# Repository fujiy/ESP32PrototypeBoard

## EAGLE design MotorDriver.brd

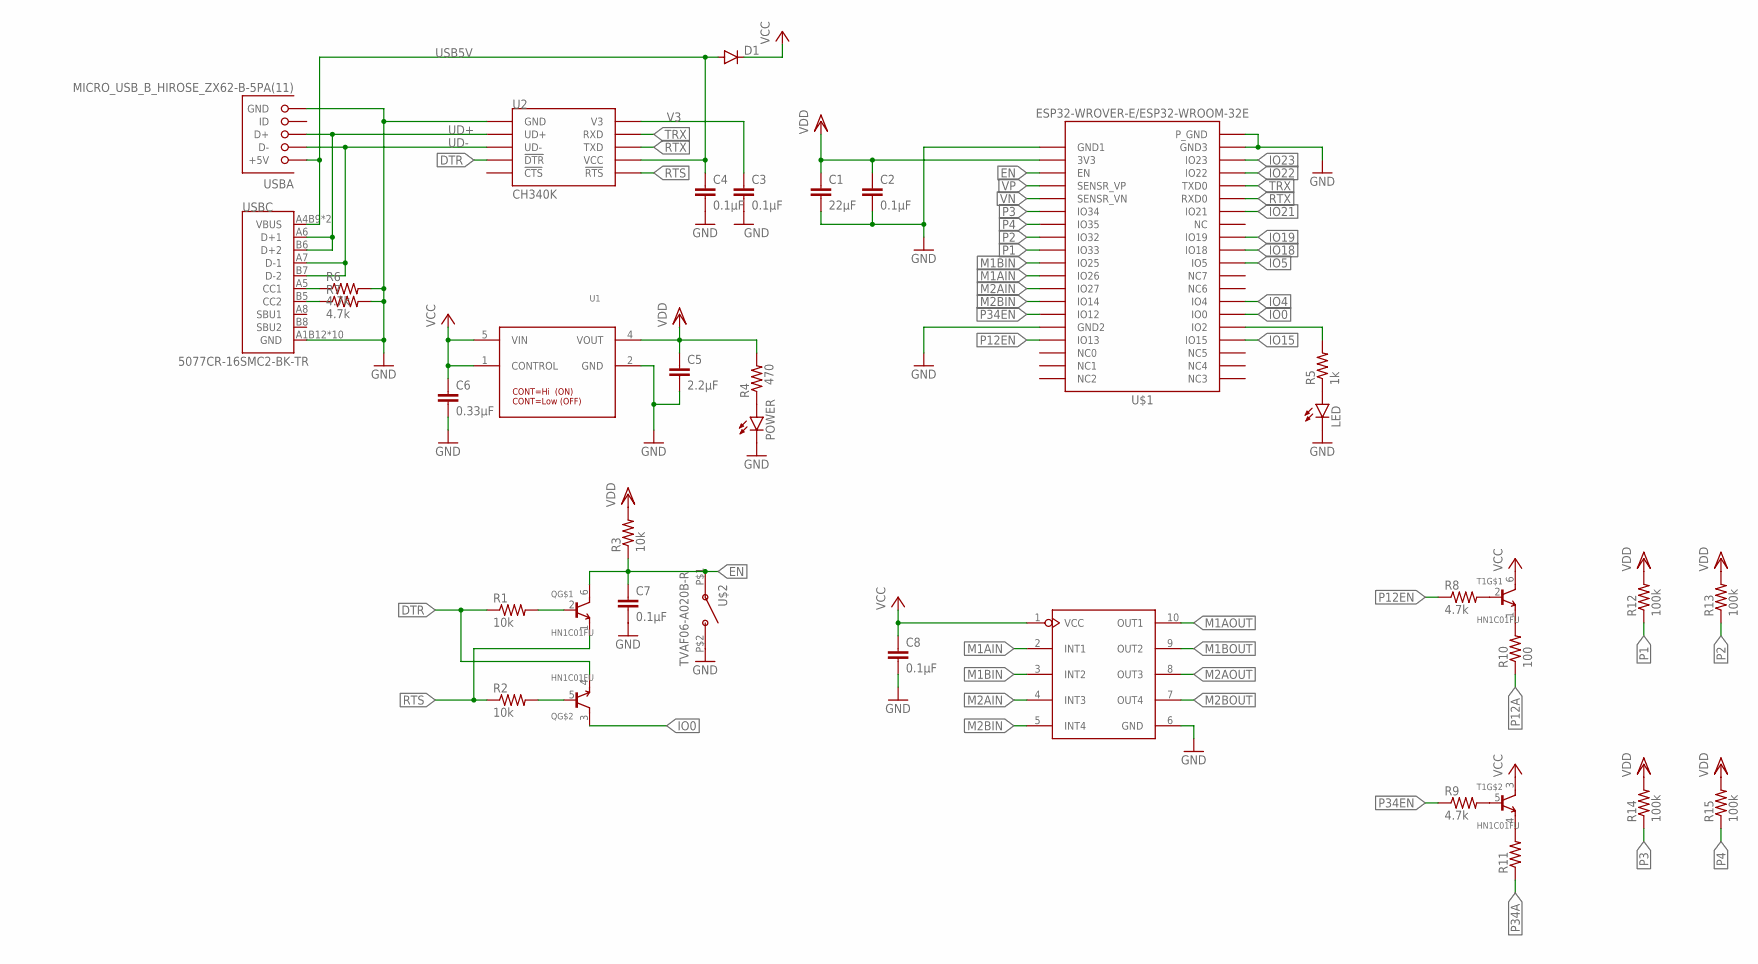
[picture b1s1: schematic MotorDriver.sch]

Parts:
C1: 22µF; C0603K
C2, C3, C4, C7: 0.1µF; C0603K
C5: 2.2µF; C0603K
C6: 0.33µF; C0603K
C8: 0.1µF; C0603
D1: DIODE-SOD123; SOD123
LED: LEDCHIPLED_0603; CHIPLED_0603
POWER: LEDCHIPLED_0603; CHIPLED_0603
Q: HN1C01FU; SOT-363
R1, R2, R3: 10k; R0603
R4: 470; R0603
R5: 1k; R0603
R6, R7, R8, R9: 4.7k; R0603
R10: 100; R0603
R11: R-US_R0603; R0603
R12, R13, R14, R15: 100k; R0603
T1: HN1C01FU; SOT-363
U1: I-10673_NJM2884U1-33; NJM2884U1-33
U2: CH340K; ESSOP-10
U3: DRIVER-LV8548MC-AH(SOIC10); SOIC10-1.0-5X4MM
U$1: ESP32-WROVER-E/ESP32-WROOM-32E
U$2: TVAF06-A020B-R
USBA: MICRO_USB_B_HIROSE_ZX62-B-5PA(11); USB_MICRO_B-HIROSE-ZX62-B-5PA(11)
USBC: 5077CR-16SMC2-BK-TR

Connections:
DTR: Q.4 (E), R1.1, U2.P4 (!DTR!)
EN: C7.1, Q.6 (C), R3.1, U$1.EN, U$2.P$1 (A)
GND: C1.2, C2.2, C3.2, C4.2, C5.2, C6.2, C7.2, C8.2, LED.C, POWER.C, R6.2, R7.2, U1.2 (GND), U2.P0 (GND), U2.P3 (GND), U3.6 (GND), U$1.GND1, U$1.GND2, U$1.GND2' (GND2), U$1.GND3, U$1.P_GND, U$2.P$2 (B), USBA.5 (GND), USBC.A1B12 (GND), USBC.B1A12 (GND), USBC.P$1 (GND), USBC.P$2 (GND), USBC.P$3 (GND), USBC.P$4 (GND), USBC.P$5 (GND), USBC.P$6 (GND), USBC.P$7 (GND), USBC.P$8 (GND)
IO0: Q.3 (C), U$1.IO0
IO2: R5.2, U$1.IO2, U$1.IO2' (IO2)
IO4: U$1.IO4
IO5: U$1.IO5
IO15: U$1.IO15, U$1.IO15' (IO15)
IO18: U$1.IO18
IO19: U$1.IO19
IO21: U$1.IO21
IO22: U$1.IO22
IO23: U$1.IO23
M1AIN: U3.2 (INT1), U$1.IO26
M1AOUT: U3.10 (OUT1)
M1BIN: U3.3 (INT2), U$1.IO25
M1BOUT: U3.9 (OUT2)
M2AIN: U3.4 (INT3), U$1.IO27
M2AOUT: U3.8 (OUT3)
M2BIN: U3.5 (INT4), U$1.IO14
M2BOUT: U3.7 (OUT4)
unnamed: LED.A, R5.1
unnamed: Q.2 (B), R1.2
unnamed: Q.5 (B), R2.2
unnamed: R8.2, T1.2 (B)
unnamed: R9.2, T1.5 (B)
unnamed: R10.2, T1.1 (E)
unnamed: R11.2, T1.4 (E)
unnamed: R6.1, USBC.A5 (CC1)
unnamed: POWER.A, R4.1
unnamed: R7.1, USBC.B5 (CC2)
P1: R12.1, U$1.IO33
P2: R13.1, U$1.IO32
P3: R14.1, U$1.IO34
P4: R15.1, U$1.IO35
P12A: R10.1
P12EN: R8.1, U$1.IO13, U$1.IO13' (IO13)
P34A: R11.1
P34EN: R9.1, U$1.IO12
RTS: Q.1 (E), R2.1, U2.P6 (!RTS!)
RTX: U2.P8 (TXD), U$1.RXD0
TRX: U2.P9 (RXD), U$1.TXD0
UD+: U2.P1 (UD+), USBA.3 (D+), USBC.A6 (D+1), USBC.B6 (D+2)
UD-: U2.P2 (UD-), USBA.2 (D-), USBC.A7 (D-1), USBC.B7 (D-2)
USB5V: C4.1, D1.A, U2.P7 (VCC), USBA.1 (+5V), USBC.A4B9 (VBUS), USBC.B4A9 (VBUS)
V3: C3.1, U2.P10 (V3)
VCC: C6.1, C8.1, D1.C, T1.3 (C), T1.6 (C), U1.1 (CONTROL), U1.5 (VIN), U3.1 (VCC)
VDD: C1.1, C2.1, C5.1, R3.2, R4.2, R12.2, R13.2, R14.2, R15.2, U1.4 (VOUT), U$1.3V3
VN: U$1.SENSOR_VN (SENSR_VN)
VP: U$1.SENSOR_VP (SENSR_VP)

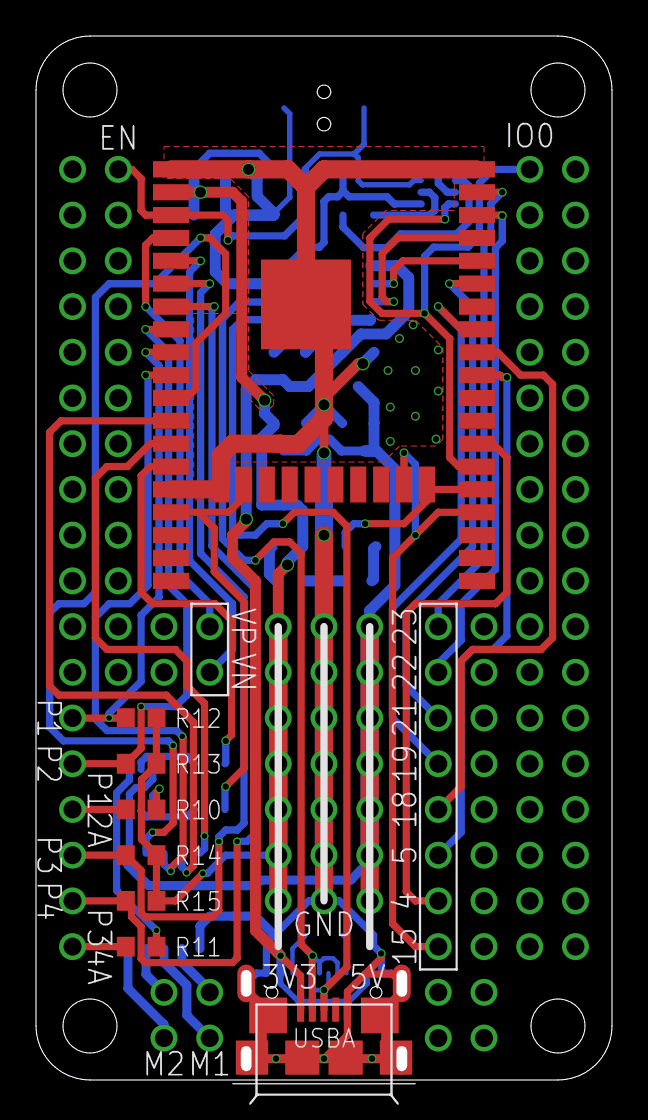
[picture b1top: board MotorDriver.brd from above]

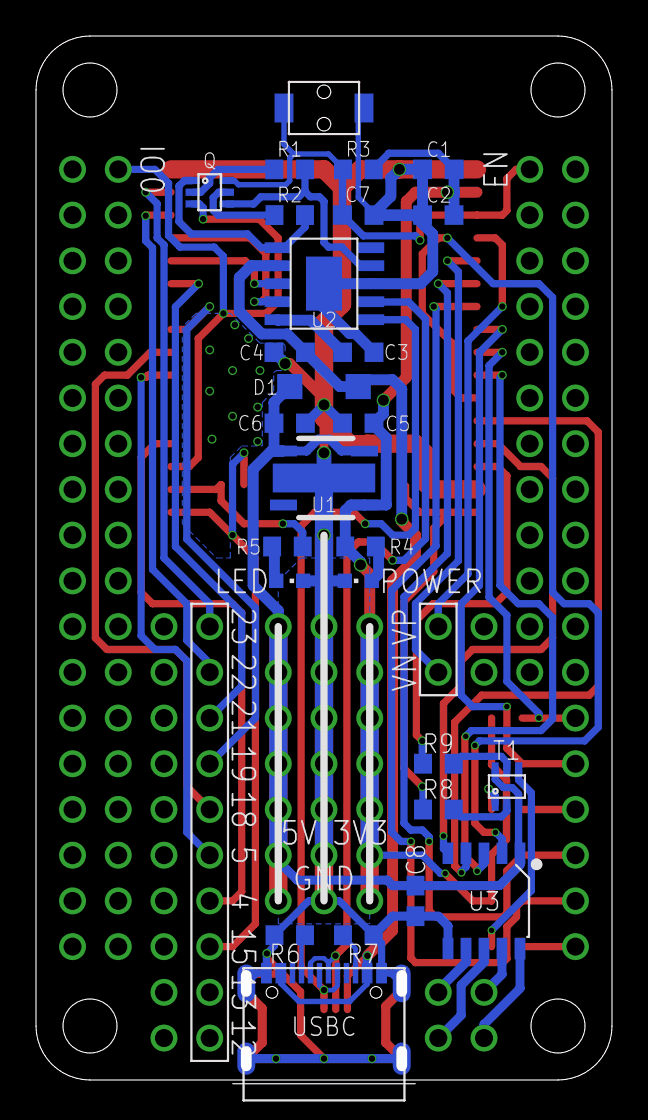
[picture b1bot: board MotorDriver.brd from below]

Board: 2 copper layers, 31.4 x 57.6 mm, 35 parts (27 on the bottom side), 35 nets.

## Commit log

2022-01-09 Fix connection
2022-01-09 Add reset switch
2022-01-15 Add Type-C connector version
2022-01-15 Add motor driver board
